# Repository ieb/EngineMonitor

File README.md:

# EngineMonitor

An engine monitor using a ESP-WROOM-32 board from ebay. It senses 1wire temperature, i2c pressure and temperature (BMP280), and has 2 digial inputs and 4 analogue inputs (ADS1115) for monitoring a typical marine diesel engine. In addition there is a JDY-40 serial RF interface for polling remote sensors.

It emits NMEA2000 messages to a NMEA200 bus, with configuration over Classic Bluetooth serial, saved to flash.

It supports PGN PGN127488 (rapid engine), PGN127489 (engine data), PGN130312 (various temperatures), PGN127508 (battery status), PGN127513 (battery configuration).

Sensors include:

* RPM from W+ terminal of alternator.
* Coolant Temperature
* Oil Pressure
* Fuel Level
* Alternator Voltage
* Alternator Temperature
* Exhaust Temperature
* Engine Room Temperature
* Environment Temperature and Pressure

Other values for the PGNs above are based on interpolation, best guess, fake, where possible. Target engine is a D2-40F, so the code is setup for that engines curves and prop. Most parameters can be changed over the Bluetooth serial CLI.

## RF

Over RF (TBD), Devices based on Arduino Pro Mini, JDY-40, ADS1115 (Arduino ADC not flexible enough). JDY-40s provide a serial 128 RF bands. In each band devices with the same RFID (WirelessID 2bytes) and DVID (Device ID 2bytes). Both the transmitter and reciever channel, RFID and DeviceID must match for packets to be transfered. These are set by AT commands to switch the trancever into that mode. The device will ignore packets that dont match and wont recieve packets that are on a different channel.

JDY-40s were chosen becuase they have a simple serial interface and are relativey low power. BT Classic would have been an alternative but requires pairing and wont work in a mesh and doesnt have the range (top of mast for some sensors). BLE, is just too complex to be bothered with. ZigBee modules are too expensive. NRF24L01+ could have been used, however the interface is SPI. If the JDY-40 cant operate in a mesh then they may need to be replaced with NRF24L01+. For the moment JDY-40 seems the simplest approach, however there is no deal on the JDY-40 RF protocol whereas the NRF24L01+ is detailed https://www.sparkfun.com/datasheets/Components/SMD/nRF24L01Pluss_Preliminary_Product_Specification_v1_0.pdf and has a TCP like RF protocol, and allows upto 6 transmitters to send to a single reciever over parallel data pipes. 

### Communication pattern.

The sensors involved need to provide data periodically, eg every 10s rather than stream continuously at 5Hz. So the simplest mechanism is to use the RFID ID/DeviceID setting in the JDY40. Each node is allocated a ID. On start it waits for a query. The base cycles through each ID requesting data and waiting for a set period for a response before moving to the next device. No blocking operations with communications going via the main loop.

### Protocol

Single line terminated by a NL. Fields comma seperated with the last field being a hex encoded crc16. 
    
      deviceid,datatype,field1,field2,...,fieldn,checksumNL

      device id is the id of the device, 0-255, hex
      datatype defines the fields, 0-255, hex
      field1..n the fields, text formatted.
      checksum a hex crc16 of the whole line excluding , before the checksum.
      NL a new line character.

* Engine Battery voltage, current, temperature, configuration
* Service Battery voltage, current, temperature, configuration

## PCB

The PCB handles power and signal cleaning. 
It is single sided and can easilly be created using basic laser printer+CuCl etching at home, or using a CNC PCB Milling machine (FlatCAM+Candle). 

Power consumption is < 50mA@5V RF sensors consume < 25mA@3.3V

Board used is a ESP-WROOM-32D based board with Wifi and Bluetooth, although Wifi is not used. Available from eBay. https://www.ebay.co.uk/itm/143297558340 30 pin DIL.
Datasheet of the chip https://www.espressif.com/sites/default/files/documentation/esp32-wroom-32d_esp32-wroom-32u_datasheet_en.pdf

Most of the remainder of this readme is notes.

# ESP32 pins

Not all ESP32 pins can be used, but most ESP32 pins can be remapped unlike Arduino boards. 

See PCB Schematic for details of how pins are used.
Pin numbers are the WROOM32 board pin numnbers, names are the pin name of the ESP32 chip.

Digital pulse in 1 -> Pin10/GPIO27
Digital pulse in 2 -> Pin9/GPIO26
RF Chip Enable (low to enable) -> Pin20/D4
RF Serial RX -> PIN21/RX2/GPIO16
RF Serail TX -> Pin22/TX2/GPIO17
RF Serial Enable -> Pin23/D5
CAN RX -> Pin24/D18
CAN TX -> Pin25/D19
1 Wire -> Pin26/D21
i2c SCL -> Pin29/D22
i2c SDA -> Pin30/D23

On the i2c bus is a BMP280 (temp/pressure) and an ADS1115 (4ch 16bit precision ADC) with a pin header for extension.
The Digital pulse is sharpened with a 74HC14 trigger.
CAN Trancever is a MCP2562
RF Serial is a JDY-40 with a Beken BK2461 controller and custom firmware. (2.4 GHz)

ESP32 ADC is non linear and frustrating to use, hence the i2c ACD.

D2 cant be used as its attached to the LED on the board.

GND on 14,17, VIN 5V on 15, 3.3V out on 16 
Other boards may vary but this seems to be a common pattern probably based on a standard Espresif design.

See signalk/SenseESP for details on how to develop.

# Connections

The board is intended to monitor the engine, other boards may monitor over the RF link, which avoids having to have many
devices connected to the N2K bus and long wires pulled through tight conduits.

## RF

### Battery Monitoring

Pro Mini with RF board using ACS758xCB at suitable range (eg ACS758ECB-200B-PFF-T, 10mV/A output bidirectional) 1 per battery bank sending data over RF on request, include a 1 wire sensor to sense terminal temperature. Should work as a single board screwed onto the battery terminals.

## 1 Wire

* 3.3v orange marked + board side
* signal white/orange marked nothng
* - green marked - case side

* Alternator Temp 
* Exhaust Temperature 
* Engine Room Temperature
* Service Battery Temperature 

Onewire sensors tend to not be rugged enough to attach directly to a engine block, see below
for coolant temp

## Pulse

* NC Blue, case side, marked 2
* W+ Orange, board side marked 1

## i2c

* BMP280 
   Engine room pressure, less that atmospheric indicates air flow problems.
   Engine room temperature (perhaps, however see 1 wire above)
* ADS1115
   ADC0 = Coolant Temperature Sensor - Blue/Orange - case side, marked C
   ADC1 = Alternator Voltage - White/orange, marked A
   ADC2 = Service battery Voltage - White/brown, marked O (was Oil)
   ADC3 = Fuel Level   - brown - esp32 side, marked F

# NMEA2000 connection

Using an AMP Superseal 4 way connector
Pin 1 +12V - Red
Pin 2 GND - Black
Pin 3 CanL - White
Pin 4 CanH - Blue
Shield GND plane on PCB

GND connected to the NMEA2000 bus may need to be reviewed depending on if there is any voltage differential between NMEA2000 GND and Engine GND due to Charging currents from the alternator. Coolant Temperature will be impacted the most followed by Fuel Level, Oil Pressure and Alternator voltage if there is a significant voltage drop. This will put the NMEA2000 GND +ve to the engine GND increasing the aparant measured coolant temperature and Fuel level when the Alternator is producing high charge output. The GND connection from Engine to Ships GND is short, but not 0R.  

# NMEA2000 PGNs

When connecting the EngineMonitor to a Raymarine MFD it reported errors for messages not expected in Class 50, Propulsion, Function 160 Engine gateway. The suspicion is that non Engine related messages need to be emitted from NMEA2000 device other than the Engine

Engine Monitor Device Class 50 Propulsion, Function 160 Engine gateway. or 140 Engine
127488 (0x1F200) Engine Parameters, Rapid Update 0.1s
127489 (0x1F201) Engine Parameters, Dynamic 0.5s
127505 (0x1F211) Fluid Level 2.5s
130316 (0x1FD0C) Temperature Extended Range

General Temperatures 75/130
130312 (0x1FD08) Temperatures

Atmospheric 85/130
130311 (0x1FD07) Environmental Parameters 10s

Batteries 35/170
127508 (0x1F214) Battery Status

# Related information

This project is targeting a D2-40 engine.

Volvo Penta D2-40 engines like many other Volvo engines have a Mechanical Diesel Interface (MDI) that provides a J1939 interface to the sensors. MDIs are limited in what they sense, and so are probable limited in what they report.

Based on the workshop manual and physical connections the sensors available to the MDI are:

* Supply Voltage
* Coolant Temp, thermistor.
* Oil Pressure Switch
* Flywheel Hall sensor
* Glow plugs (current sensor tbc)
* Starter relay
* Buttons on the control pannel.

Note, there is no ECU on D1,D2 engines as the base engine is a fully mechanical Perkins unit with a mechanical injection pump.

Larger Volvo Penta engines with a full ECU will have many more sensors. A great explanation of J1939 can be found at https://www.csselectronics.com/screen/page/simple-intro-j1939-explained/language/en which is presented on a CAN physical transport.  J1939 is the heavy truck protocol, 250K baud, 29bit PGN. At L7 OSI stack it is J1979 (ISO 15031-5), and at L2 it is CAN (ISO 15765-4). Some commodity ELM327 scanners may be able to read and decode the packets with the correct plugs (eg viecar + CarScanner app).

J1939 is not NMEA2000, as the message structure is different and hence to connect a D2-40 MDI CAN Bus to a NMEA2000 CAN Bus requires a converter. Given how limited the set of sensors is, and how simple the MDI is it may not be worth it for MDI based engines. Volvo Penta Gateways retail at about 300 GBP, the Digital 

# Bench testing

Obviously it is not ideal to bench test with a real engine so its mocked up using a signal generator and a scope. The W+ terminal on the alternator is produced with a 2V sine wave into a 2N2222 switch powered by 14v so that the output is roughly a 14V sine wave.   The temperature sensor is a resistor bridge with the thermistor replaced by a 20 turn pot. 5V supply through a zener powered by 12v trough a 470R. The other voltages are generated with 20 turn 10K pots.

# Tests and todo

* [x] Pulse to Frequency
* [x] ADC measurement on all channels
* [x] Tested on engine
* [x] Fix: make engine port not starboard
* [?] Fix: potential fix of 8 unkown status messages from the device, possibly caused by using 1 device for all messages.
* [x] make device message period configurable
* [x] Shorten rpm send and sample period without loosing precision, currently sampling at 2s, needs to send at 0.2s
* [x] Fix engine on detection.
* [x] Support Bluetooth enable button
* [x] Check 1-wire temperature sensors
* [x] Coolant Temperature conversion
* [x] Alternator pulse verified
* [x] Fuel Level conversion
* [x] Send Fuel Tank level when engine on.
* [x] Install and test.
* [x] Add sensor simulation to test offline without live data.
* [x] Fix engine on reported when not on
* [x] Fix 150c when engine off, so its 0 when off.
* [x] Fix baromiter update too low to Raymarine, lowered to 10s defaul from 60s.
* [x] Fix 8 error messages from engine on init, look like they are 1-8 Unknown Errors, see p113 of the Raymarine LightHouse2 manual, possibly fixed by https://github.com/ttlappalainen/NMEA2000/commit/94c9bd5e1256ad8e4b3b8f7bd3f69339b2645b26
* [x] Reconfigure fuel level measurement, needs some additional wiring to power the fuel sensor from the 5v supply.
* [x] Emit fuel tank when the engine is off.
* [x] Add alarms and configuration expecially for values not supported by displays.
* [x] Make bluetooth touch sensitive
* [x] Install and test2
* [x] Make default thermal sensor match Luna
* [x] Fix engine on bugs
* [x] Removed Touch BT enable and go back to switch to see if it makes i2c initialisation stable, using Touch seems to have introduced instability into the sensors.
* [x] Bench test
* [ ] Install and test3

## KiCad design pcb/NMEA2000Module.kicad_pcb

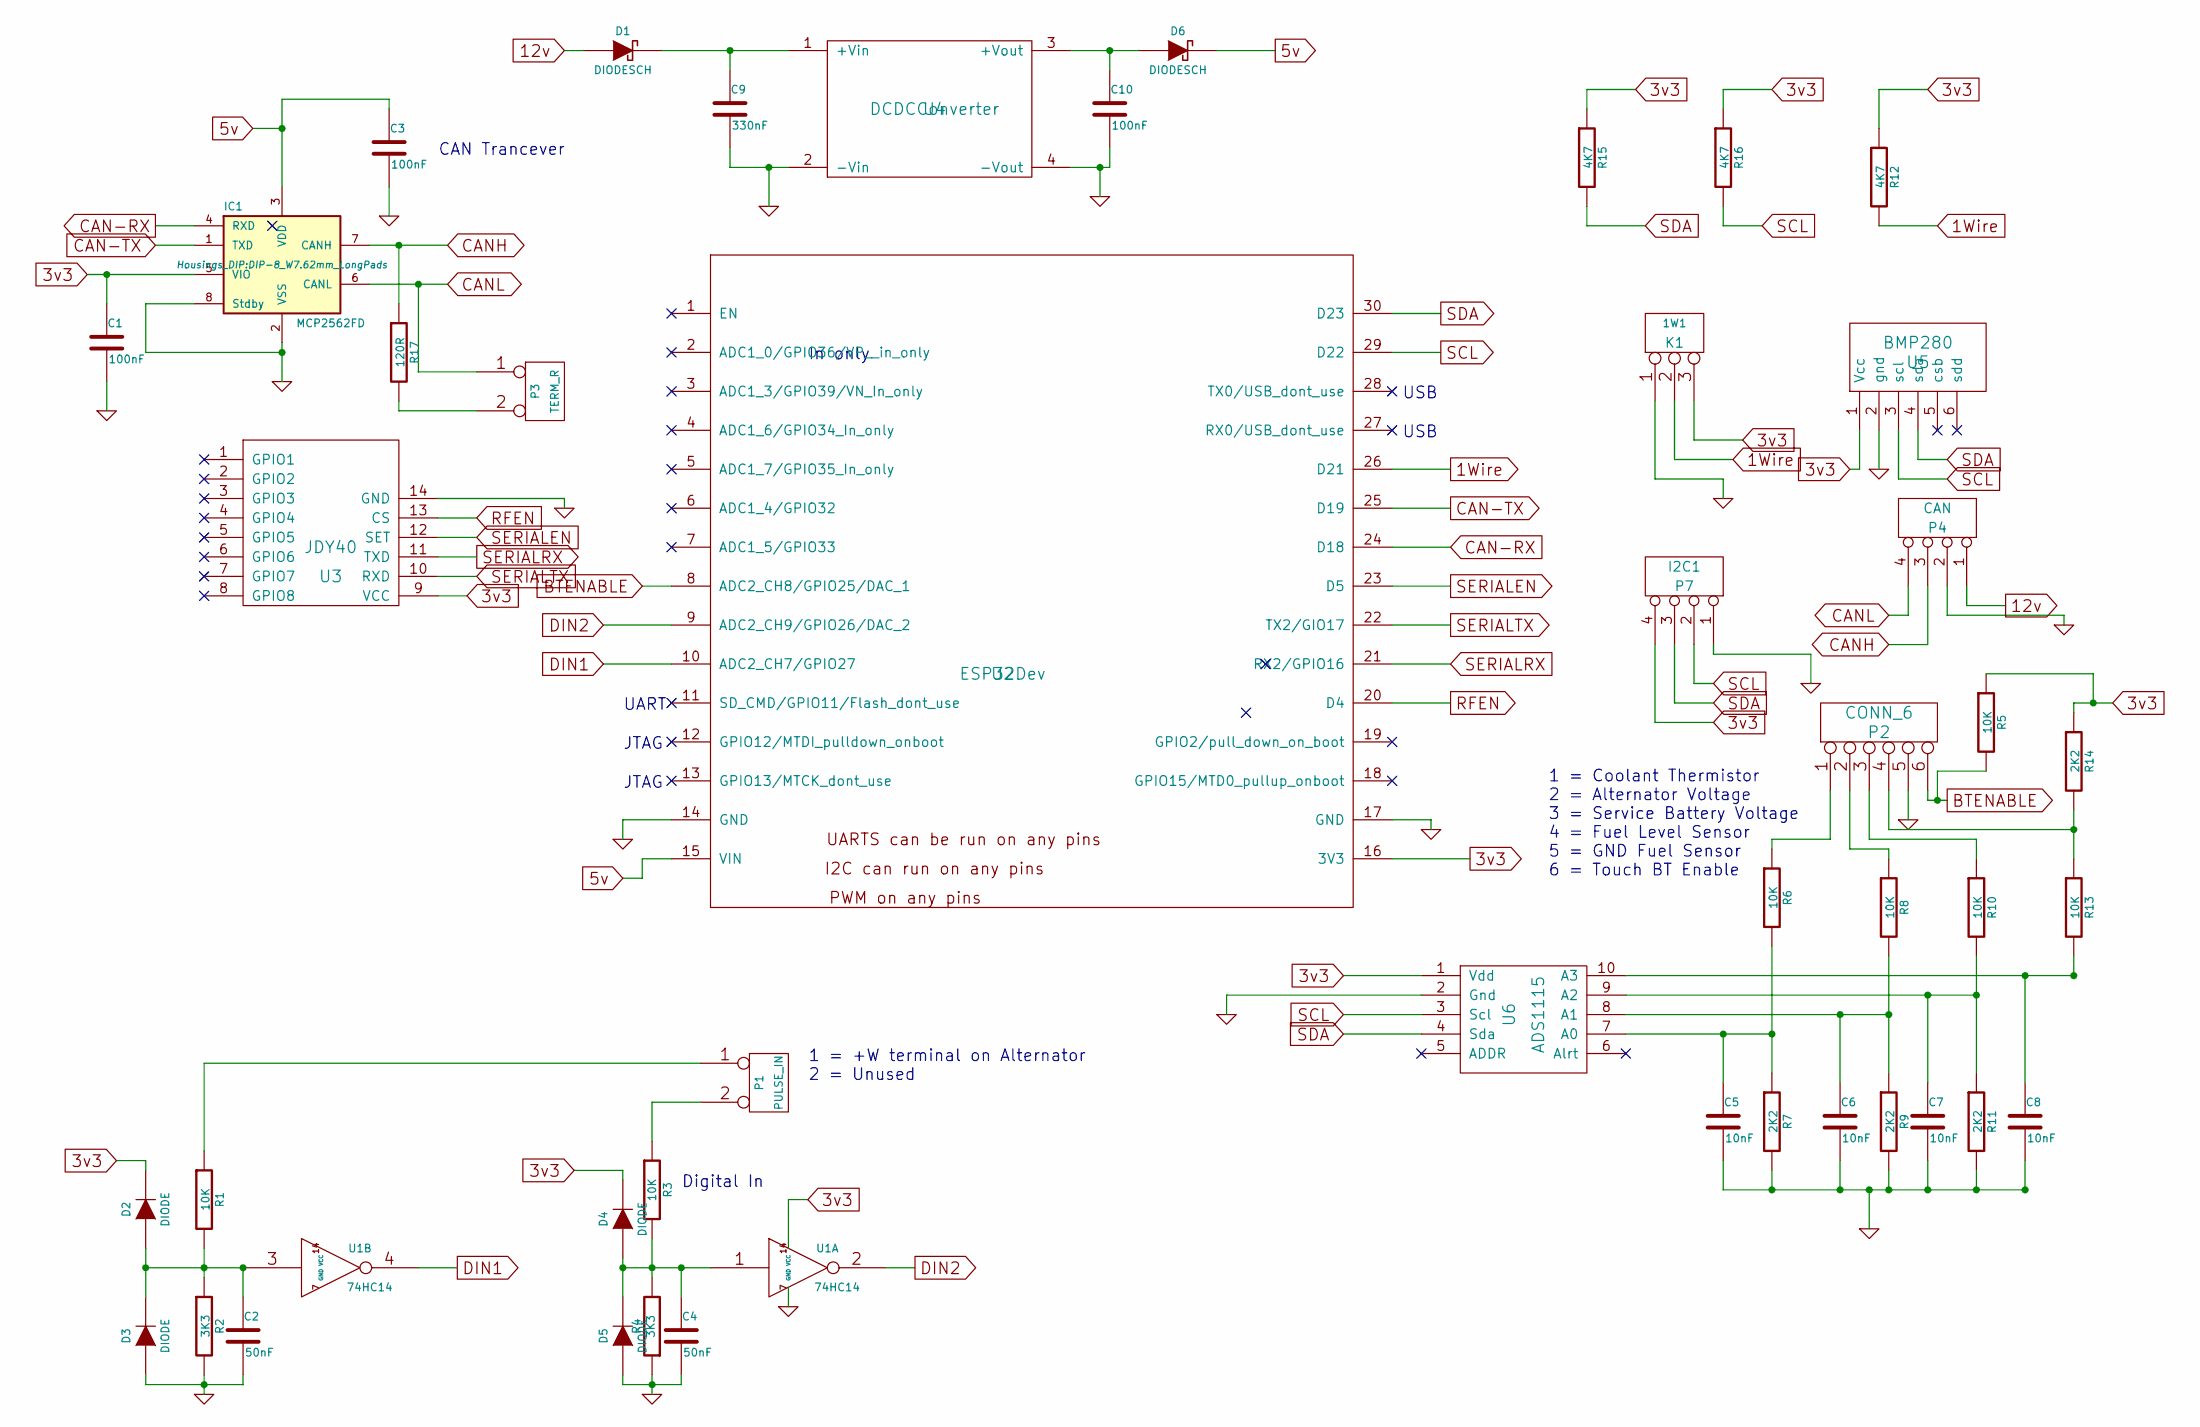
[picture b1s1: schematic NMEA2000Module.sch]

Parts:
C1, C3, C10: 100nF; C_0805_HandSoldering
C2, C4: 50nF; C_0805_HandSoldering
C5, C6, C7, C8: 10nF; C_0805_HandSoldering
C9: 330nF; C_0805_HandSoldering
D1, D6: DIODESCH; Resistor_Horizontal_RM7mm
D2, D3, D4, D5: DIODE; SOT-23
IC1: MCP2562FD; DIP-8_W7.62mm_LongPads
K1: 1W1; Pin_Header_Straight_1x03_Pitch2.54mm
P1: PULSE_IN; Pin_Header_Straight_1x02_Pitch2.54mm
P2: CONN_6; Pin_Header_Straight_1x06_Pitch2.54mm
P3: TERM_R; Pin_Header_Straight_1x02_Pitch2.54mm
P4: CAN; Pin_Header_Straight_1x04_Pitch2.54mm
P7: I2C1; Pin_Header_Straight_1x04_Pitch2.54mm
R1, R3, R5, R6, R8, R10, R13: 10K; R_0805_HandSoldering
R2, R4: 3K3; R_0805_HandSoldering
R7, R9, R11, R14: 2K2; R_0805_HandSoldering
R12, R15, R16: 4K7; R_0805_HandSoldering
R17: 120R; R_0805_HandSoldering
U1: 74HC14; DIP-14_W7.62mm_LongPads
U2: ESP32Dev; DIP-30_1_ELL
U3: JDY40; JDY-40-TH
U4: DCDCConverter; DC-DC-Converter
U5: BMP280
U6: ADS1115

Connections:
1Wire: K1.2 (PM), R12.2, U2.26 (D21)
3v3: C1.1, D2.2 (K), D4.2 (K), IC1.5 (VIO), K1.3, P7.4, R5.1, R12.1, R14.1, R15.1, R16.1, U1.14 (VCC), U2.16 (3V3), U3.9 (VCC), U5.1 (Vcc), U6.1 (Vdd)
5v: C3.1, D6.2 (K), IC1.3 (VDD), U2.15 (VIN)
12v: D1.1 (A), P4.1
BTENABLE: P2.6, R5.2, U2.8 (ADC2_CH8/GPIO25/DAC_1)
CAN-RX: IC1.4 (RXD), U2.24 (D18)
CAN-TX: IC1.1 (TXD), U2.25 (D19)
CANH: IC1.7 (CANH), P4.3, R17.1
CANL: IC1.6 (CANL), P3.1, P4.4
DIN1: U1.4, U2.10 (ADC2_CH7/GPIO27)
DIN2: U1.2, U2.9 (ADC2_CH9/GPIO26/DAC_2)
GND: C1.2, C2.2, C3.2, C4.2, C5.2, C6.2, C7.2, C8.2, C9.2, C10.2, D3.1 (A), D5.1 (A), IC1.2 (VSS), IC1.8 (Stdby), K1.1, P2.5, P4.2, P7.1, R2.2, R4.1, R7.2, R9.2, R11.2, U1.7 (GND), U2.14 (GND), U2.17 (GND), U3.14 (GND), U4.2 (-Vin), U4.4 (-Vout), U5.2 (gnd), U6.2 (Gnd)
unnamed: C2.1, D2.1 (A), D3.2 (K), R1.2, R2.1, U1.3
unnamed: C4.1, D4.1 (A), D5.2 (K), R3.2, R4.2, U1.1
unnamed: C5.1, R6.2, R7.1, U6.7 (A0)
unnamed: C6.1, R8.2, R9.1, U6.8 (A1)
unnamed: C7.1, R10.2, R11.1, U6.9 (A2)
unnamed: C8.1, R13.2, U6.10 (A3)
unnamed: C9.1, D1.2 (K), U4.1 (+Vin)
unnamed: C10.1, D6.1 (A), U4.3 (+Vout)
unnamed: P1.1, R1.1
unnamed: P1.2 (PM), R3.1
unnamed: P2.1, R6.1
unnamed: P2.2, R8.1
unnamed: P2.3, R10.1
unnamed: P2.4, R13.1, R14.2
unnamed: P3.2 (PM), R17.2
RFEN: U2.20 (D4), U3.13 (CS)
SCL: P7.2, R16.2, U2.29 (D22), U5.3 (scl), U6.3 (Scl)
SDA: P7.3, R15.2, U2.30 (D23), U5.4 (sda), U6.4 (Sda)
SERIALEN: U2.23 (D5), U3.12 (SET)
SERIALRX: U2.21 (RX2/GPIO16), U3.11 (TXD)
SERIALTX: U2.22 (TX2/GIO17), U3.10 (RXD)

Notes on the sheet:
CAN Trancever
Digital In
JTAG
USB
UART
In only
1 = Coolant Thermistor 2 = Alternator Voltage 3 = Service Battery Voltage 4 = Fuel Level Sensor 5 = GND Fuel Sensor 6 = Touch BT Enable
1 = +W terminal on Alternator 2 = Unused

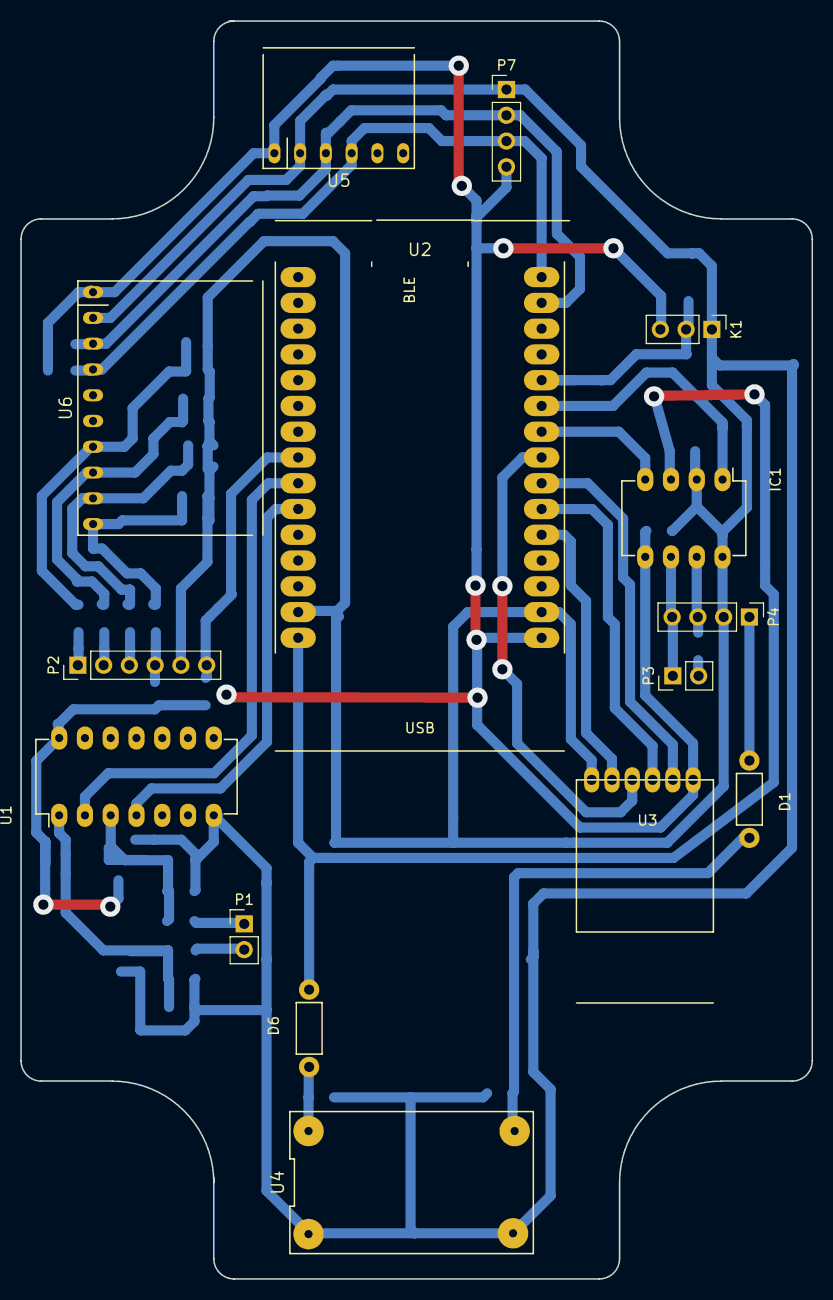
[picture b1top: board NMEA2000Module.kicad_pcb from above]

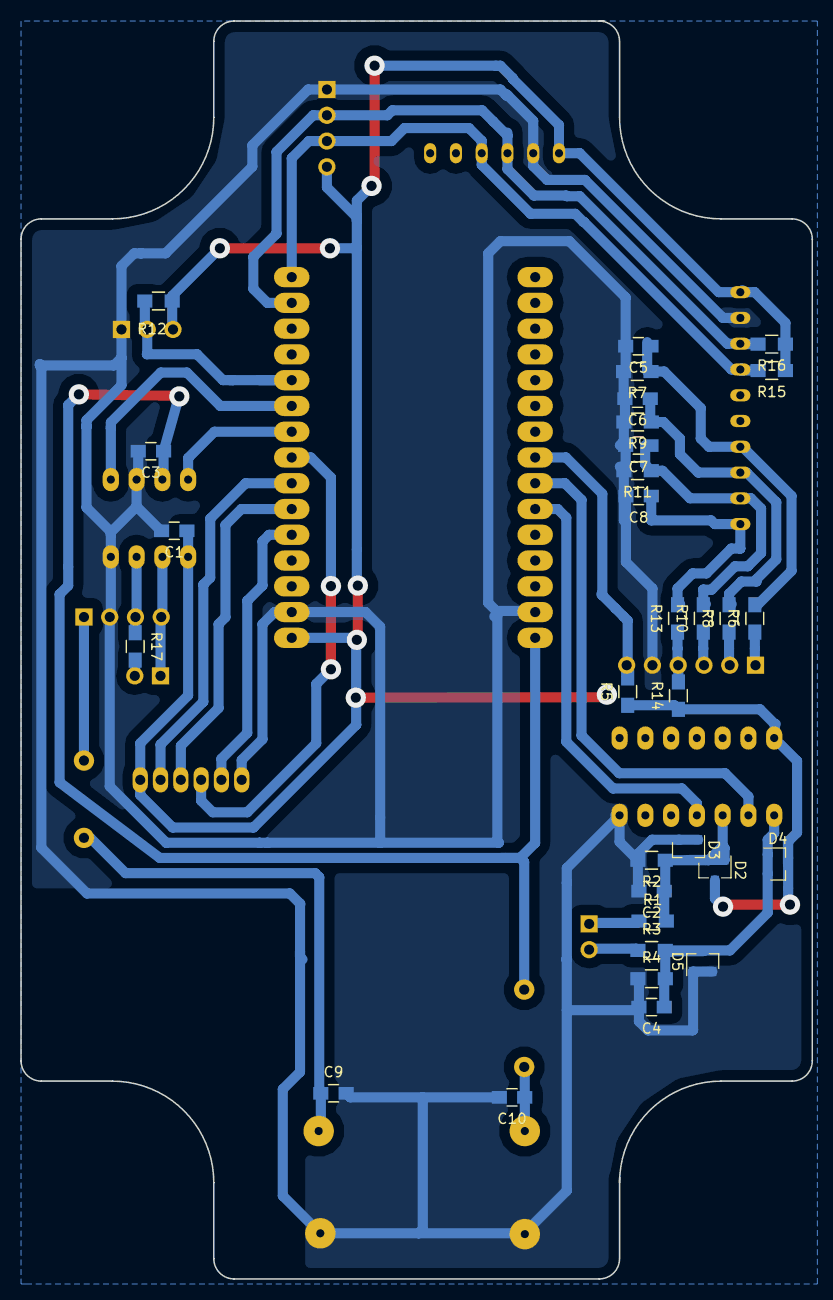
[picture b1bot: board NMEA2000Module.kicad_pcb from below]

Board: 2 copper layers, 78.0 x 124.0 mm, 46 parts (31 on the bottom side), 33 nets.

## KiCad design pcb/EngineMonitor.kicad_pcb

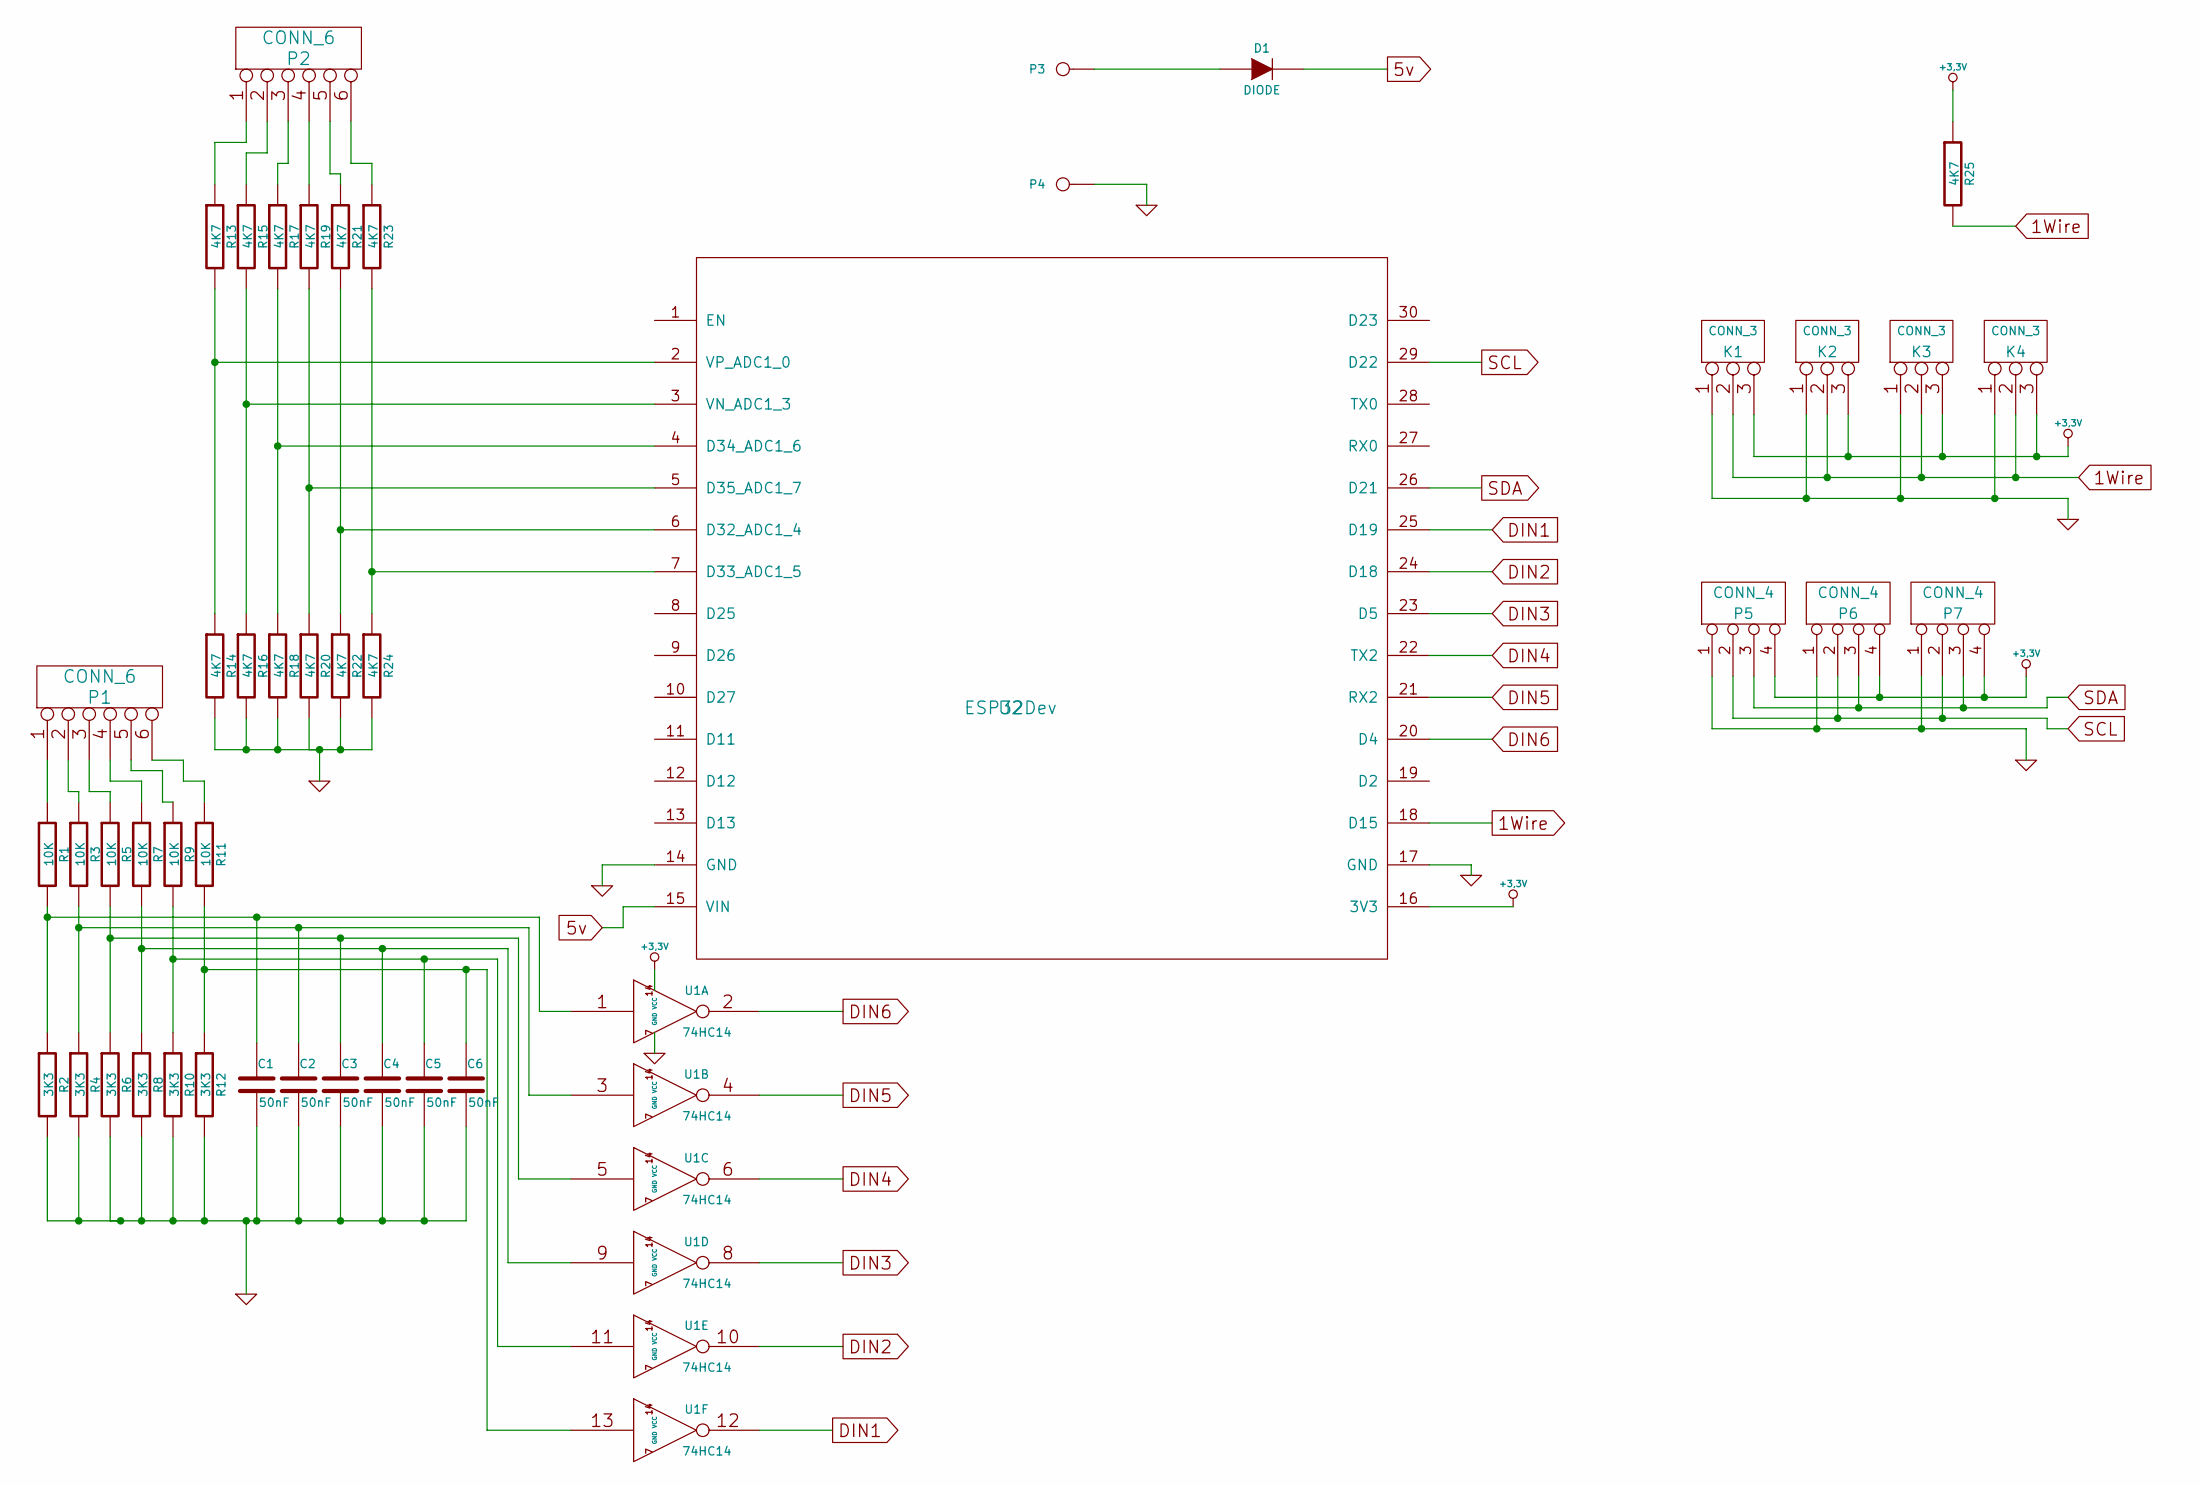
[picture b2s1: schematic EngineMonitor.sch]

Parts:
C1, C2, C3, C4, C5, C6: 50nF; Resistor_Horizontal_RM7mm
D1: DIODE; Resistor_Horizontal_RM7mm
K1, K2, K3, K4: CONN_3; Pin_Header_Straight_1x03_Pitch2.54mm
P1, P2: CONN_6; Pin_Header_Straight_1x06_Pitch2.54mm
P3, P4: CONN_1; Pin_Header_Straight_1x01_Pitch2.54mm
P5, P6, P7: CONN_4; Pin_Header_Straight_1x04_Pitch2.54mm
R1, R3, R5, R7, R9, R11: 10K; Resistor_Horizontal_RM7mm
R2, R4, R6, R8, R10, R12: 3K3; Resistor_Horizontal_RM7mm
R13, R14, R15, R16, R17, R18, R19, R20, R21, R22, R23, R24, R25: 4K7; Resistor_Horizontal_RM7mm
U1: 74HC14; DIP-14_W7.62mm_LongPads
U2: ESP32Dev; DIP-30_1_ELL

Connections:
1Wire: K1.2 (PM), K2.2 (PM), K3.2 (PM), K4.2 (PM), R25.2, U2.18 (D15)
5v: D1.2 (K), U2.15 (VIN)
+3.3V: K1.3, K2.3, K3.3, K4.3, P5.4, P6.4, P7.4, R25.1, U1.14 (VCC), U2.16 (3V3)
DIN1: U1.2, U2.20 (D4)
DIN2: U1.4, U2.21 (RX2)
DIN3: U1.6, U2.22 (TX2)
DIN4: U1.8, U2.23 (D5)
DIN5: U1.10, U2.24 (D18)
DIN6: U1.12, U2.25 (D19)
GND: C1.2, C2.2, C3.2, C4.2, C5.2, C6.2, K1.1, K2.1, K3.1, K4.1, P4.1, P5.1, P6.1, P7.1, R2.2, R4.2, R6.2, R8.2, R10.2, R12.2, R14.2, R16.2, R18.2, R20.2, R22.2, R24.2, U1.7 (GND), U2.14 (GND), U2.17 (GND); also elsewhere on the board
unnamed: C1.1, R1.2, R2.1, U1.1
unnamed: C2.1, R3.2, R4.1, U1.3
unnamed: C3.1, R5.2, R6.1, U1.5
unnamed: C4.1, R7.2, R8.1, U1.9
unnamed: C5.1, R9.2, R10.1, U1.11
unnamed: C6.1, R11.2, R12.1, U1.13
unnamed 16: D1.1 (A), P3.1; also elsewhere on the board
unnamed: P1.1, R1.1
unnamed: P1.2, R3.1
unnamed: P1.3, R5.1
unnamed: P1.4, R7.1
unnamed: P1.5, R9.1
unnamed: P1.6, R11.1
unnamed: P2.1, R13.1
unnamed: P2.2, R15.1
unnamed: P2.3, R17.1
unnamed: P2.4, R19.1
unnamed: P2.5, R21.1
unnamed: P2.6, R23.1
unnamed: R13.2, R14.1, U2.2 (VP_ADC1_0)
unnamed: R15.2, R16.1, U2.3 (VN_ADC1_3)
unnamed: R17.2, R18.1, U2.4 (D34_ADC1_6)
unnamed: R19.2, R20.1, U2.5 (D35_ADC1_7)
unnamed: R21.2, R22.1, U2.6 (D32_ADC1_4)
unnamed: R23.2, R24.1, U2.7 (D33_ADC1_5)
SCL: P5.2, P6.2, P7.2, U2.29 (D22)
SDA: P5.3, P6.3, P7.3, U2.26 (D21)

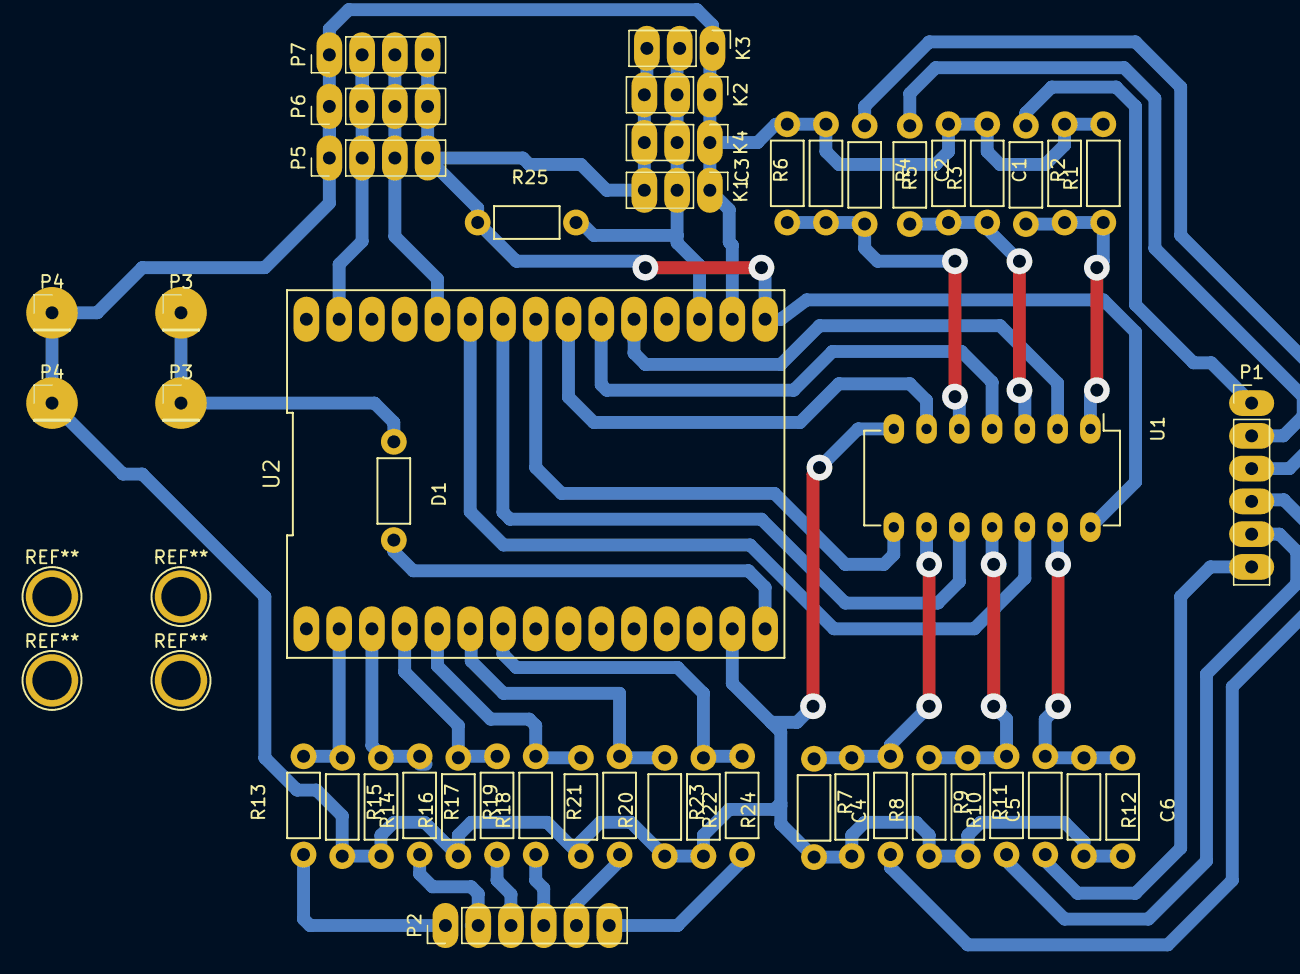
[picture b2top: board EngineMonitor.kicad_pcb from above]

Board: 2 copper layers, 47 parts (0 on the bottom side), 37 nets.

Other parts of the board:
P3#2, P4#2: CONN_1; Pin_Header_Straight_1x01_Pitch2.54mm

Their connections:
GND: P4#2.1; also elsewhere on the board
unnamed 16: P3#2.1; also elsewhere on the board

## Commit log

2020-07-11 Workign version, may need some caliration tweaks
2020-07-13 Working version with all sensors in box ready to be installed
2020-07-13 Working version with all sensors in box ready to be installed (fixup)
2020-07-17 Redisigned board and fixed sensors
2020-08-26 After adjustments onboard for voltages, not very accurate due to ADC non linearity
2020-08-26 New Board, i2C ADC + CAN connection
2021-02-16 Adapted from SignalK to NMEA2000 device
2021-02-17 Passing test coverage for engineconfig
2021-02-18 Added saving engine hours to NVS
2021-02-27 Added RF code not tested, and high voltage protection diodes
2021-02-27 Fixed crash with interrupt handler not pinned into ram
2021-02-28 Tested pulse sensor and ADC operating correctly against mock engine
2021-03-02 Added BMP280 sensor and changed to LDO regulator
2021-03-04 Adjusted fuel level calcs to use bridge
2021-03-06 Calibrations on voltages
2021-03-08 Cleaned up output and tested on live NMEA2000 bus
2021-03-10 Fixes after first live test
2021-03-11 Added BT switch and engine on support
2021-03-14 Dropped oil pressure, teste fuel level
2021-03-16 Emitting fuel tank level pgn, tested
2021-03-24 Added sensor simulation, fixed pressure update period
2021-03-26 Added better support for simulation and alarms
2021-03-27 fixed engine hours, made bluetooth touch enabled, workign verison
2021-04-02 Fixed instabilities from BT Touch enable
2021-04-05 Update to pcb to reflect prototype
2023-09-09 Fixed 49day overflows
